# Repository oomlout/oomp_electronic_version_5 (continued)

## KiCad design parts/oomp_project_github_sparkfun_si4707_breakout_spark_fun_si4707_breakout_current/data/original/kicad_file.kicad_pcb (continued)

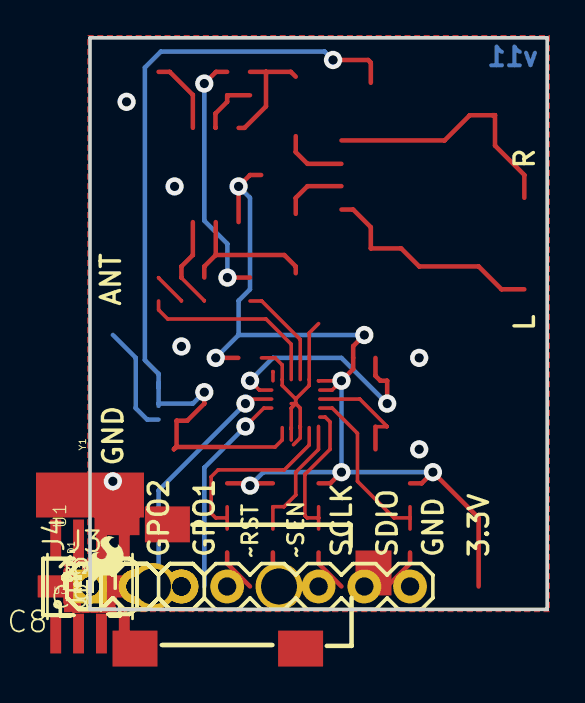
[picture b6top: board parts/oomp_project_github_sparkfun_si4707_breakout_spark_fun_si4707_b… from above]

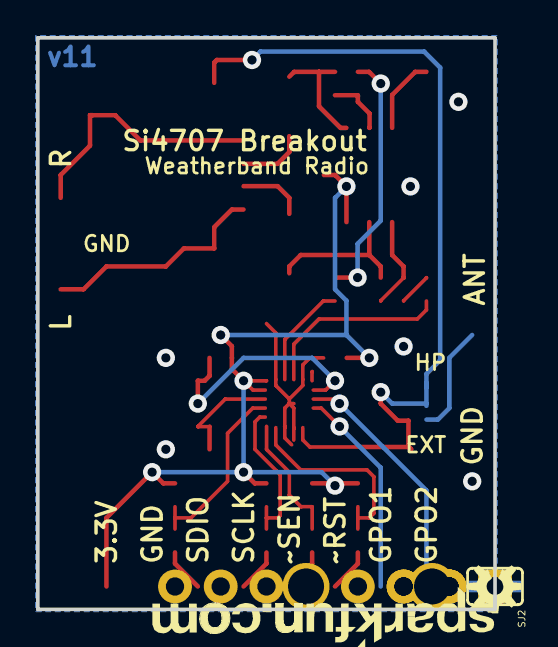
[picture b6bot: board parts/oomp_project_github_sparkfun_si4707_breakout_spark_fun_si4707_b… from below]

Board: 2 copper layers, 25.4 x 31.8 mm, 40 parts (3 on the bottom side), 30 nets.

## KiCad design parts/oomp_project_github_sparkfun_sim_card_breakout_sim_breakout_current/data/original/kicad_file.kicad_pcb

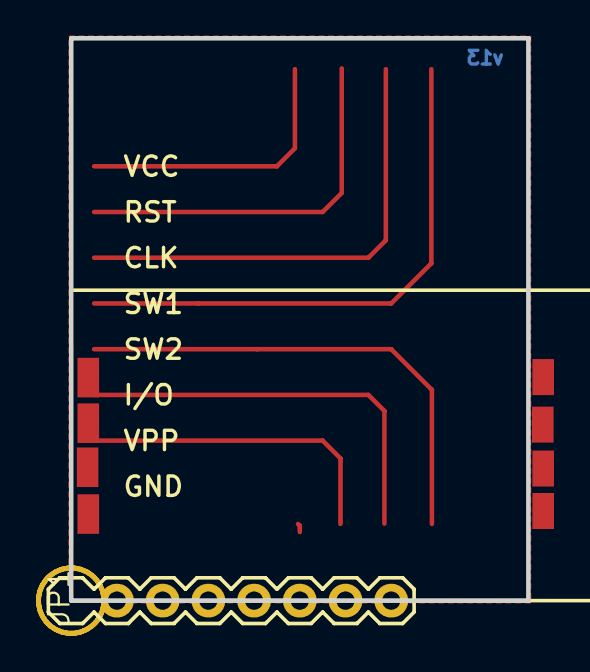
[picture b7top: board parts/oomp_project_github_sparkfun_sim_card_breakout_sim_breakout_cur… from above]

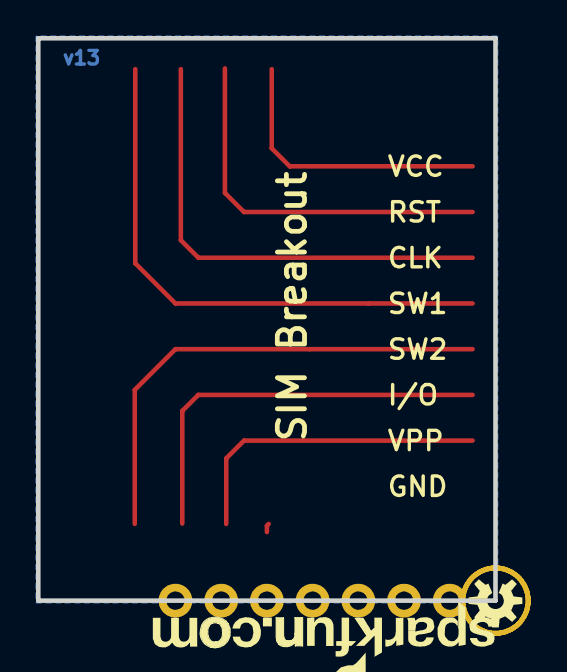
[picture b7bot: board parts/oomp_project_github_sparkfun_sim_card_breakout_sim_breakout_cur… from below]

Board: 2 copper layers, 25.4 x 31.2 mm, 9 parts (2 on the bottom side), 8 nets.

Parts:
FID1, FID2: FIDUCIALUFIDUCIAL; MICRO-FIDUCIAL
FRAME2: FRAME-LETTER; CREATIVE_COMMONS
JP1: 1X08
LOGO1: OSHW-LOGOS; OSHW-LOGO-S
STANDOFF1, STANDOFF2: STAND-OFF
U2: SIMHOLDER; SIMHOLDER2
U$1: SFE-NEW-WEBLOGO

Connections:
CLK: JP1.3, U2.3
GND: JP1.8, U2.8
I/O: JP1.6, U2.6
RST: JP1.2, U2.2
SW1: JP1.4, U2.4
SW2: JP1.5, U2.5
VCC: JP1.1, U2.1
VPP: JP1.7, U2.7

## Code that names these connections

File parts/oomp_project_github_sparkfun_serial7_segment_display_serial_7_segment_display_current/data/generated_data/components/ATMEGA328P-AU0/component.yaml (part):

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    dnp: false
    pins:
    - number: '1'
      name: PD3(INT1)
      electrical_type: bidirectional
      graphic_style: line
      local_position:
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      connected_to:
      - reference: LED1
        pin_number: '6'
        pin_name: DIG3
    - number: '2'
      name: PD4(XCK/T0)
      electrical_type: bidirectional
      graphic_style: line
      local_position:
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      connected_to:
      - reference: LED1
        pin_number: '8'
        pin_name: DIG4
    - number: '3'
      name: GND
      electrical_type: bidirectional
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        pin_number: '2'
        pin_name: '2'
    - number: '7'
      name: PB6(XTAL1/TOSC1)
      electrical_type: bidirectional
      graphic_style: line
      local_position:
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        pin_number: '2'
        pin_name: '2'
    - number: '8'
      name: PB7(XTAL2/TOSC2)
      electrical_type: bidirectional
      graphic_style: line
      local_position:
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        pin_number: '2'
        pin_name: '2'
    - number: '9'
      name: PD5(T1)
      electrical_type: bidirectional
      graphic_style: line
      local_position:
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        pin_number: '2'
        pin_name: '2'
    - number: '10'
      name: PD6(AIN0)
      electrical_type: bidirectional
      graphic_style: line
      local_position:
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        pin_number: '2'
        pin_name: '2'
    - number: '11'
      name: PD7(AIN1)
      electrical_type: bidirectional
      graphic_style: line
      local_position:
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        pin_number: '2'
        pin_name: '2'
    - number: '12'
      name: PB0(ICP)
      electrical_type: bidirectional
      graphic_style: line
      local_position:
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        pin_number: '2'
        pin_name: '2'
    - number: '13'
      name: PB1(OC1A)
      electrical_type: bidirectional
      graphic_style: line
      local_position:
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      connected_to:
      - reference: LED1
        pin_number: '10'
        pin_name: APOS-A
    - number: '14'
      name: PB2(SS/OC1B)
      electrical_type: bidirectional
      graphic_style: line
      local_position:
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        pin_number: '9'
        pin_name: '9'
    - number: '15'
      name: PB3(MOSI/OC2)
      electrical_type: bidirectional
      graphic_style: line
      local_position:
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        pin_number: '8'
        pin_name: '8'
    - number: '16'
      name: PB4(MISO)
      electrical_type: bidirectional
      graphic_style: line
      local_position:
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        pin_number: '5'
        pin_name: '5'
    - number: '17'
      name: PB5(SCK)
      electrical_type: bidirectional
      graphic_style: line
      local_position:
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        pin_number: '1'
        pin_name: '1'
    - number: '23'
      name: PC0(ADC0)
      electrical_type: bidirectional
      graphic_style: line
      local_position:
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        pin_number: '2'
        pin_name: '2'
    - number: '24'
      name: PC1(ADC1)
      electrical_type: bidirectional
      graphic_style: line
      local_position:
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        pin_number: '2'
        pin_name: '2'
    - number: '25'
      name: PC2(ADC2)
      electrical_type: bidirectional
      graphic_style: line
      local_position:
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      connected_to:
      - reference: LED1
        pin_number: '1'
        pin_name: DIG1
    - number: '26'
      name: PC3(ADC3)
      electrical_type: bidirectional
      graphic_style: line
      local_position:
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      connected_to:
      - reference: LED1
        pin_number: '2'
        pin_name: DIG2
    - number: '27'
      name: PC4(ADC4/SDA)
      electrical_type: bidirectional
      graphic_style: line
      local_position:
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        pin_number: '1'
        pin_name: '1'
    - number: '28'
      name: PC5(ADC5/SCL)
      electrical_type: bidirectional
      graphic_style: line
      local_position:
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        pin_number: '2'
        pin_name: '2'
    - number: '29'
      name: PC6(/RESET)
      electrical_type: bidirectional
      graphic_style: inverted
      local_position:
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        pin_number: '1'
        pin_name: '1'
    - number: '30'
      name: PD0(RXD)
      electrical_type: bidirectional
      graphic_style: line
      local_position:
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        pin_number: '10'
        pin_name: '10'
    - number: '31'
      name: PD1(TXD)
      electrical_type: bidirectional
      graphic_style: line
      local_position:
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        pin_number: '4'
        pin_name: '4'
    - number: '32'
      name: PD2(INT0)
      electrical_type: bidirectional
      graphic_style: line
      local_position:
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      connected_to:
      - reference: LED1
        pin_number: '4'
        pin_name: COL-A
    size:
      local_graphics:
        measurement: symbol graphics only; excludes pins, properties, and text
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    pin_name: '9'
  - reference: LED1
    pin_number: '1'
    pin_name: DIG1
  - reference: LED1
    pin_number: '10'
    pin_name: APOS-A
  - reference: LED1
    pin_number: '2'
    pin_name: DIG2
  - reference: LED1
    pin_number: '4'
    pin_name: COL-A
  - reference: LED1
    pin_number: '6'
    pin_name: DIG3
  - reference: LED1
    pin_number: '8'
    pin_name: DIG4
  - reference: R1
    pin_number: '1'
    pin_name: '1'
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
